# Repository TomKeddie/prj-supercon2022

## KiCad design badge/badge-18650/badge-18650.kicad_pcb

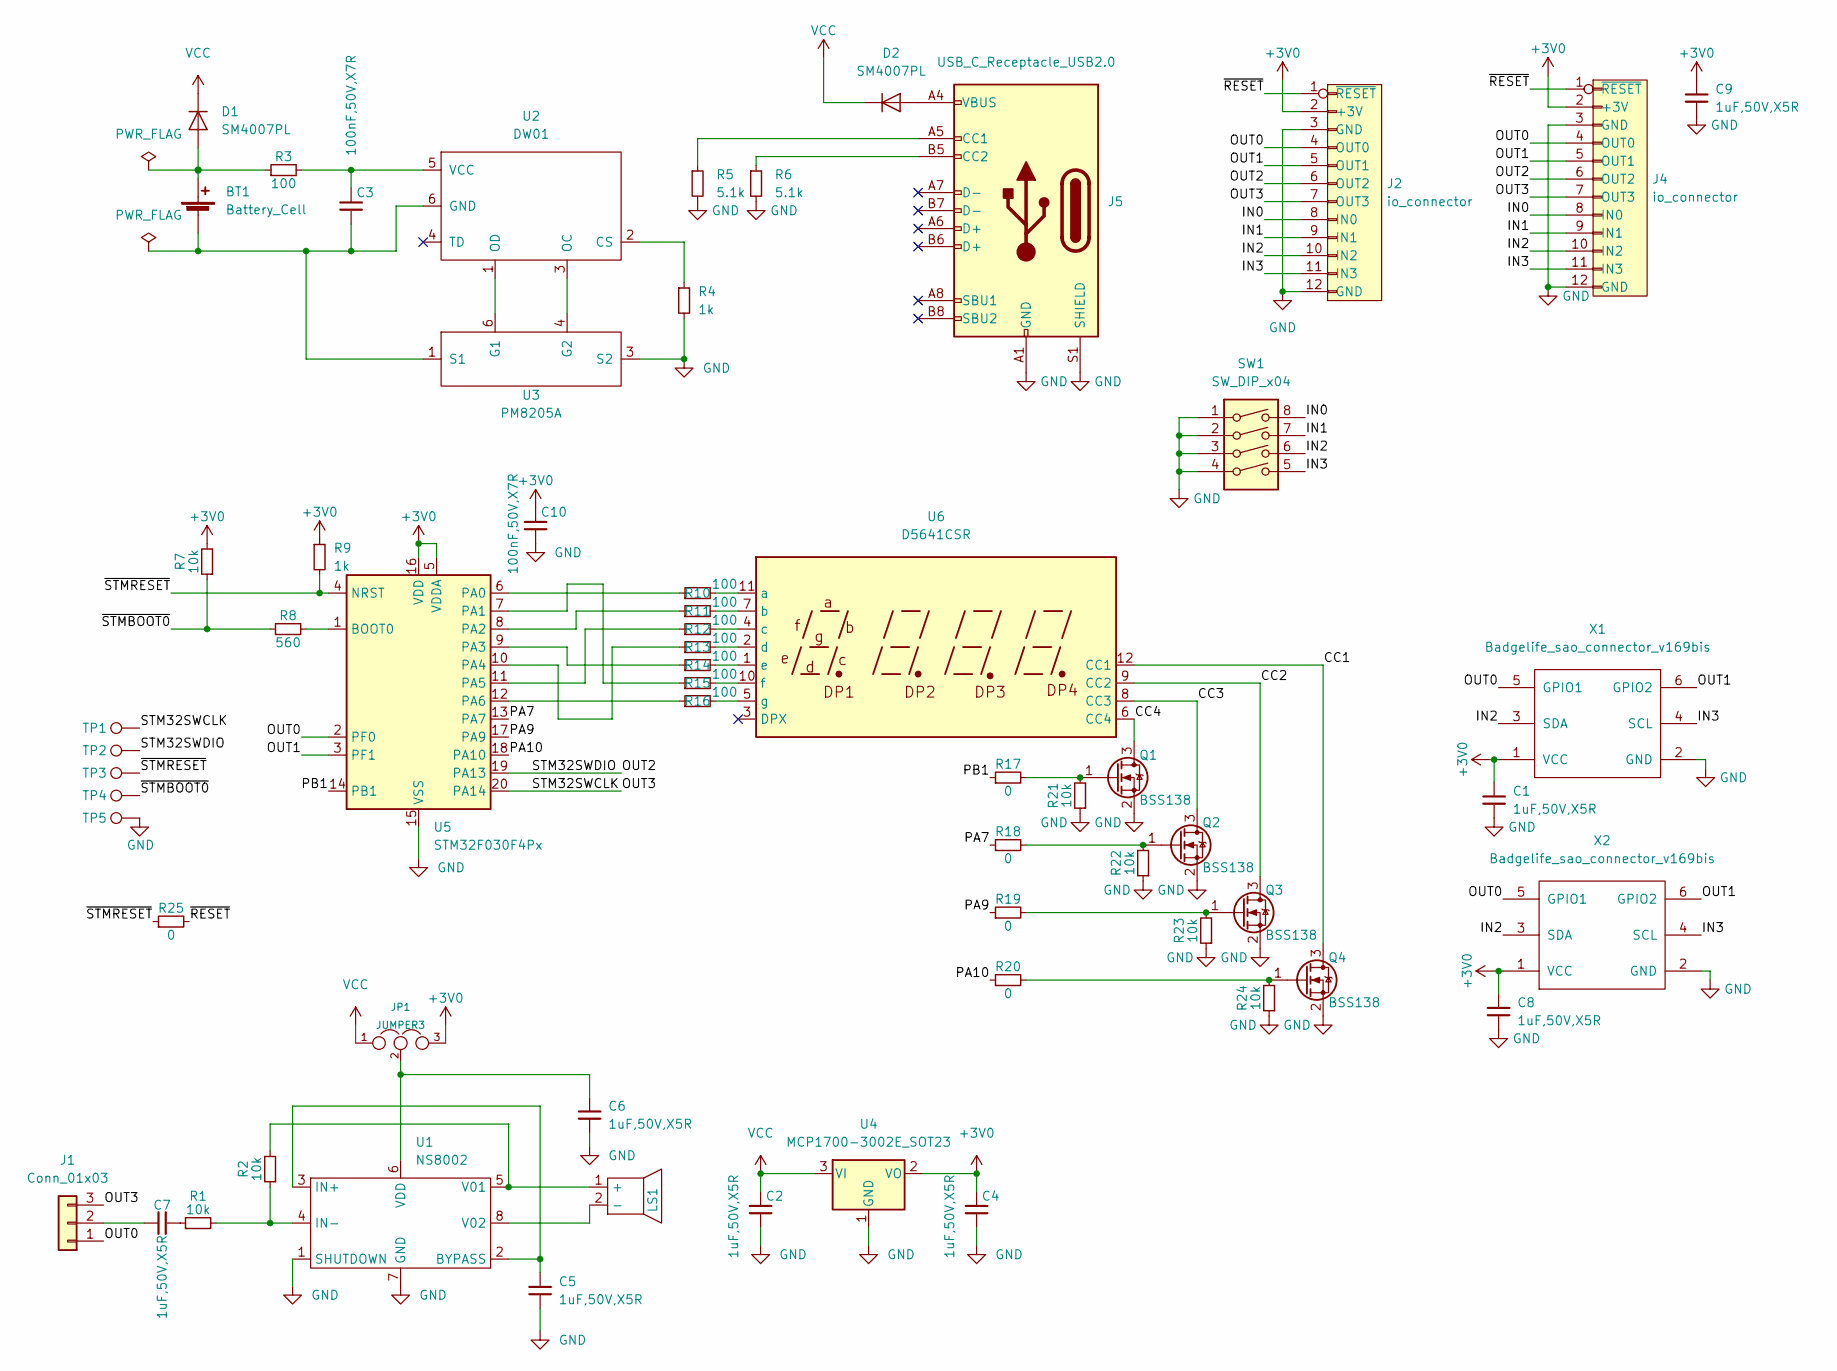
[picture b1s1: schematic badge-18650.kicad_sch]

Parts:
BT1: Battery_Cell; BatteryHolder_Keystone_1042_1x18650
C1, C2, C4, C5, C6, C7, C8, C9: 1uF,50V,X5R; C_0603_1608Metric; MFGPN CL10A105KB8NNNC; LCSC C15849
C3, C10: 100nF,50V,X7R; C_0603_1608Metric; MFGPN CC0603KRX7R9BB104; LCSC C14663
D1, D2: SM4007PL; Nexperia_CFP3_SOD-123W; LCSC C64898
J1: Conn_01x03; PinHeader_1x03_P2.54mm_Horizontal
J2: io_connector; PinSocket_1x12_P2.54mm_Horizontal
J4: io_connector; PinHeader_1x12_P2.54mm_Horizontal
J5: USB_C_Receptacle_USB2.0; USB_C_Receptacle_LCSC_C165948
JP1: JUMPER3; SolderJumper-3_P2.0mm_Open_TrianglePad1.0x1.5mm
LS1: SPEAKER; SPEAKER_36MM_8R
Q1, Q2, Q3, Q4: BSS138; SOT-23; LCSC C400505
R1, R2, R7, R21, R22, R23, R24: 10k; R_0603_1608Metric; MFGPN 0603WAF1002T5E; LCSC C25804
R3: 100; R_0603_1608Metric; MFGPN 0603WAF1000T5E; LCSC C22775
R4, R9: 1k; R_0603_1608Metric; MFGPN 0603WAF1001T5E; LCSC C21190
R5, R6: 5.1k; R_0603_1608Metric; MFGPN 0603WAF5101T5E; LCSC C23186
R8: 560; R_0603_1608Metric; MFGPN 0603WAF5600T5E; LCSC C23204
R10, R11, R12, R13, R14, R15, R16: 100; R_0603_1608Metric; MFGPN 0603WAF2200T5E; LCSC C22962
R17, R18, R19, R20, R25: 0; R_0603_1608Metric; MFGPN 0603WAF0000T5E; LCSC C21189
SW1: SW_DIP_x04; DIP-8_W7.62mm_LongPads
TP1, TP2, TP3, TP4, TP5: TestPoint; TestPoint_Pad_D3.0mm
U1: NS8002; SO-8_3.9x4.9mm_P1.27mm; LCSC C87265
U2: DW01; SOT-23-6; LCSC C181096
U3: PM8205A; SOT-23-6; Mfg PN SILICON; LCSC C2827645
U4: MCP1700-3002E_SOT23; SOT-23; LCSC C62244
U5: STM32F030F4Px; TSSOP-20_4.4x6.5mm_P0.65mm
U6: D5641CSR
X1, X2: Badgelife_sao_connector_v169bis; Badgelife-SAOv169-BADGE-2x3

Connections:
+3V0: C1.1, C4.1, C8.1, C9.1, C10.1, J2.2 (+3V), J4.2 (+3V), JP1.3, R7.2, R9.1, U4.2 (VO), U5.5 (VDDA), U5.16 (VDD), X1.1 (VCC), X2.1 (VCC)
/CC1: Q4.3 (D), U6.12 (CC1)
/CC2: Q3.3 (D), U6.9 (CC2)
/CC3: Q2.3 (D), U6.8 (CC3)
/CC4: Q1.3 (D), U6.6 (CC4)
/IN0: J2.8 (IN0), J4.8 (IN0), SW1.8
/IN1: J2.9 (IN1), J4.9 (IN1), SW1.7
/IN2: J2.10 (IN2), J4.10 (IN2), SW1.6, X1.3 (SDA), X2.3 (SDA)
/IN3: J2.11 (IN3), J4.11 (IN3), SW1.5, X1.4 (SCL), X2.4 (SCL)
/OUT0: J1.1, J2.4 (OUT0), J4.4 (OUT0), U5.2 (PF0), X1.5 (GPIO1), X2.5 (GPIO1)
/OUT1: J2.5 (OUT1), J4.5 (OUT1), U5.3 (PF1), X1.6 (GPIO2), X2.6 (GPIO2)
/OUT2: J2.6 (OUT2), J4.6 (OUT2), TP2.1, U5.19 (PA13)
/OUT3: J1.3, J2.7 (OUT3), J4.7 (OUT3), TP1.1, U5.20 (PA14)
/PA7: R18.1, U5.13 (PA7)
/PA9: R19.1, U5.17 (PA9)
/PA10: R20.1, U5.18 (PA10)
/PB1: R17.1, U5.14 (PB1)
/~RESET: J2.1 (~RESET), J4.1 (~RESET), R25.2
/~STMBOOT0: R7.1, R8.1, TP4.1
/~STMRESET: R9.2, R25.1, TP3.1, U5.4 (NRST)
GND: C1.2, C2.2, C4.2, C5.2, C6.2, C8.2, C9.2, C10.2, J2.3 (GND), J2.12 (GND), J4.3 (GND), J4.12 (GND), J5.A1 (GND), J5.A12 (GND), J5.B1 (GND), J5.B12 (GND), J5.S1 (SHIELD), Q1.2 (S), Q2.2 (S), Q3.2 (S), Q4.2 (S), R4.2, R5.2, R6.2, R21.1, R22.1, R23.1, R24.1, SW1.1, SW1.2, SW1.3, SW1.4, TP5.1, U1.1 (SHUTDOWN), U1.7 (GND), U3.3 (S2), U4.1 (GND), U5.15 (VSS), X1.2 (GND), X2.2 (GND)
unnamed: BT1.1 (+), D1.2 (A), R3.1
unnamed: BT1.2 (-), C3.2, U2.6 (GND), U3.1 (S1)
unnamed: C3.1, R3.2, U2.5 (VCC)
unnamed: C5.1, U1.2 (BYPASS), U1.3 (IN+)
unnamed: C6.1, JP1.2, U1.6 (VDD)
unnamed: C7.1, J1.2
unnamed: C7.2, R1.1
unnamed: D2.2 (A), J5.A4 (VBUS), J5.A9 (VBUS), J5.B4 (VBUS), J5.B9 (VBUS)
unnamed: J5.A5 (CC1), R5.1
unnamed: J5.B5 (CC2), R6.1
unnamed: LS1.1 (+), R2.2, U1.5 (V01)
unnamed: LS1.2 (-), U1.8 (V02)
unnamed: Q1.1 (G), R17.2, R21.2
unnamed: Q2.1 (G), R18.2, R22.2
unnamed: Q3.1 (G), R19.2, R23.2
unnamed: Q4.1 (G), R20.2, R24.2
unnamed: R1.2, R2.1, U1.4 (IN-)
unnamed: R4.1, U2.2 (CS)
unnamed: R8.2, U5.1 (BOOT0)
unnamed: R10.1, U5.6 (PA0)
unnamed: R10.2, U6.11 (a)
unnamed: R11.1, U5.8 (PA2)
unnamed: R11.2, U6.7 (b)
unnamed: R12.1, U5.11 (PA5)
unnamed: R12.2, U6.4 (c)
unnamed: R13.1, U5.10 (PA4)
unnamed: R13.2, U6.2 (d)
unnamed: R14.1, U5.9 (PA3)
unnamed: R14.2, U6.1 (e)
unnamed: R15.1, U5.7 (PA1)
unnamed: R15.2, U6.10 (f)
unnamed: R16.1, U5.12 (PA6)
unnamed: R16.2, U6.5 (g)
unnamed: U2.1 (OD), U3.6 (G1)
unnamed: U2.3 (OC), U3.4 (G2)
VCC: C2.1, D1.1 (K), D2.1 (K), JP1.1, U4.3 (VI)

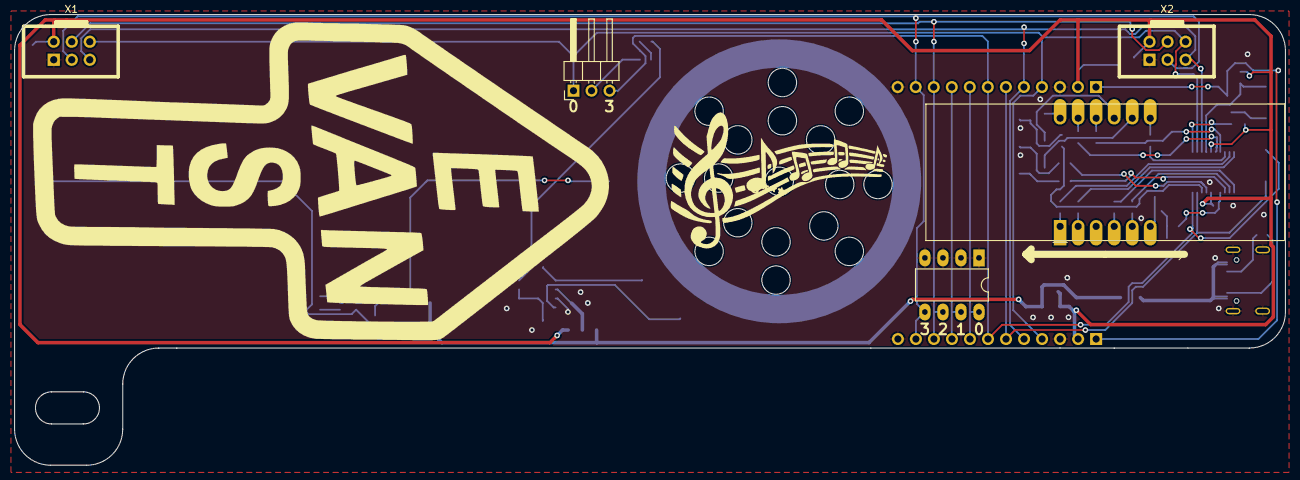
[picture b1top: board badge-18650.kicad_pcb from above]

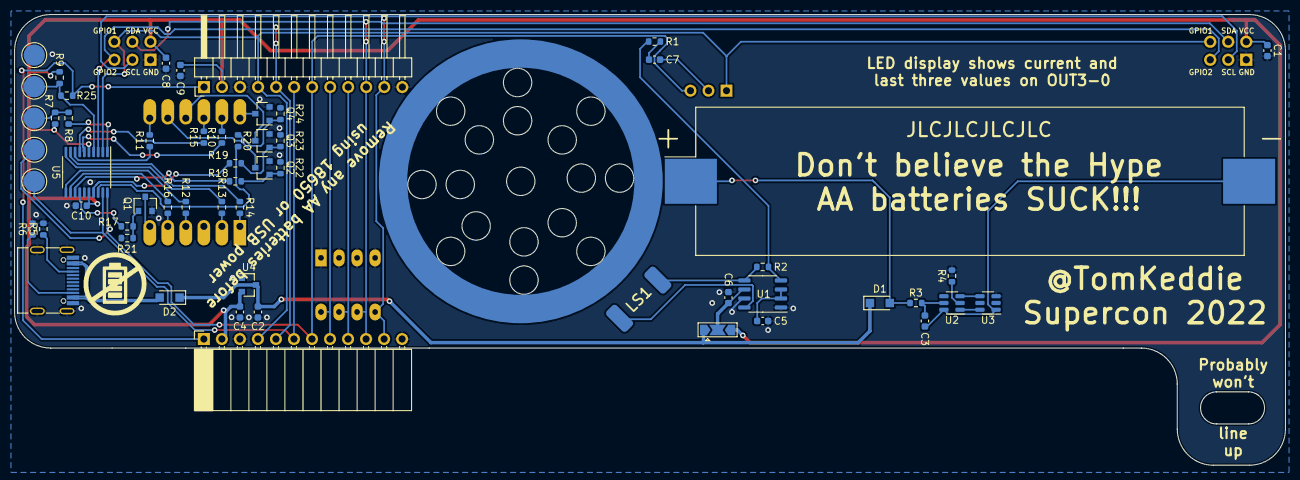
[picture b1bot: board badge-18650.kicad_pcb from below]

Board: 2 copper layers, 179.1 x 63.5 mm, 62 parts (57 on the bottom side), 57 nets.

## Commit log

2022-10-14 badge addon first attempt to submit
2022-10-14 badge add on, as submitted.
2022-10-22 badge: add updated doco
2022-10-23 badge: add furrysalamander assembler
2022-10-26 badge/stm32: add stm32 code for badge addon
2022-11-04 zephyr: add requirements.txt
2022-11-04 Rename doc, fix gitmodules
2022-11-04 zephyr: update requirements to add esptool
2022-11-04 badge: add 2022-Supercon6-Badge-Tools
2022-11-05 badge/code: add default_14 uploaded from flash section 14
2022-11-05 badge/code: add count/xor simple examples
2022-11-05 badge/doc: add latest round of documentation
2022-11-05 badge/code: add basic tone generator
2022-11-05 badge/code: add C to tones
2022-11-05 Start micropython workshop
2022-11-06 badge/code: add final mary tones
2022-11-06 badge/code: rename tones to mary
